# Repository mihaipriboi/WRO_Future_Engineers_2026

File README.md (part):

<center><h1> Nerdvana Cancer 2026 </center>

This repository contains the documentation for the Nerdvana Cancer team's robot for the 2026 World Robot Olympiad Future Engineers competition. The robot, was designed and built by a team of three students.

## Table of Contents
* [The Team](#team)
* [The Challenge](#challenge)
* [The Robot](#robot-image)
* [Performance Video](#video)
* [The Team's Evolution Over the Years](#team-evolution)
  * [2022 Paula (Pretty Awesome Ultra Low Accurate robot) - International (Germany) - 8th Place](#2022-international)
  * [2023 Paula Mia (Pretty Awesome Ultra Low Accurate Minimum Intelligence Augmentation) - National - 1st Place](#2023-national)
  * [2023 Paula Mia 2 (Pretty Awesome Ultra Locomotion Autonomous Mapping Intelligence Augmentation) - International (Panama) - 17th Place](#2023-international)
  * [2024 TBD - National - 1st Place](#2024-national)
  * [2024 MOOYA (Mechanized Optimization for Outstanding Yield and Adaptation) - International (Turkey) - 7th Place](#2024-international)
  * [2025 MOOYA* (Mechanized Optimization for Outstanding Yield and Adaptation) - National - 1st Place](#2025-national)
  * [2025 L.A.C.H.E. (Lightweight Autonomous Carbon-Hybrid Entity) - International](#2025-international)
  * [2026 M.D.S (Memory, Dead-reckoning & Steering) - Current Robot](#2026-current)
* [Mobility Management](#mobility-management)
  * [Powertrain](#powertrain-mechanical)
    * [Drivetrain](#drivetrain-mechanical)
    * [Motor](#motor-mechanical)
    * [Motor Driver](#motor-driver-mechanical)
  * [Steering](#steering-mechanical)
    * [Servo Motor](#servo-motor)
  * [Chassis](#chassis-mechanical)
* [Power and Sense Management](#power-and-sense-management)
  * [Li-Po Battery](#li-po-battery)
  * [Arduino Nano ESP32](#arduino-nano-esp32)
  * [IMU](#imu-sensor)
  * [OpenMV Cam H7 R2](#openmv-cam-rt1062)
  * [Voltage Regulator](#voltage-regulator)
  * [PCB Design](#pcb)
  * [Circuit Diagram](#circuit-diagram)
* [Code for each component](#code-for-each-component)
  * [Drive Motor](#drive-motor-code)
  * [Servo Motor](#servo-motor-code)
  * [Camera](#camera-code)
  * [IMU](#gyro-sensor-code)
* [Obstacle Management](#obstacle-management)
  * [Qualification Round](#quali-management)
  * [Final Round](#final-management)
  * [Additional code](#additional-code)
* [What We Changed This Year](#whats-new)
  * [Tuning and telemetry over WiFi](#wifi-dashboard)
  * [A drift-free gyro that finds its own straight](#self-straight)
  * [Our own localization and route memory](#self-localization)
  * [Rethinking the parking](#smart-parking)
  * [Where this is heading](#next-steps)
* [Robot Construction Guide](#robot-construction-guide)
  * [Step 0: Print the 3D parts](#3d-printing)
  * [Step 1: Assemble the steering system](#steering-system-assembly)
  * [Step 2: Assemble the powertrain](#powertrain-assembly)
  * [Step 3: Attach the electronics](#electronics-attachment)
  * [Step 4: Upload the code](#code-upload)
* [Cost Report](#cost-report)
  * [3D Printing Costs](#3d-printing-costs)
  * [Other Parts Tested](#other-parts-tested)
  * [Tools and Equipment](#tools-and-equipment)
  * [Summary of Costs](#summary-of-costs)
* [Randomizer](#randomizer)
* [Resources](#resources)
  * [3D Models](#3d-models-resources)
  * [Images](#images-resources)
* [License](#copyright)

---

## The Team 

### Priboi Luca Mihai

<b>Age:</b> 20

<b>University:</b> 2nd year, Politehnica University of Bucharest

<b>Description:</b> Hello! I am Mihai! I've been participating at WRO since 2015 and I am very excited to be part of the Nerdvana Romania team. My academic passions are programming, physics and robotics, but I also enjoy playing the piano 🎹, whatching movies 🎬, traveling ✈️ and Formula 1 🏎️🏁.

---

### Bălan Teodor Ovidiu

<b>Age:</b> 20

<b>University:</b> 2nd year, University of Bucharest

<b>Description:</b> Wassup y'all! My name is Teodor, and I love traveling and experiencing new things. Since I was a kid, I've always been drawn to solving puzzles, playing basketball, discovering new inventions, and thinking of creative ways to do things. Also, I know how to do a backflip. 🤠

---

### Orășeanu Andrei

<b>Age:</b> 17

<b>School:</b> 11th grade, Colegiul Național Gheorghe Șincai

<b>Description:</b> Hello! I'm Andrei, and I've been part of WRO since 2023. What pulled me in from the very first season was the part where you build something with your own hands and then have to teach it to think for itself, that moment when the robot finally does the thing on its own never gets old. My main passions are robotics and physics, but outside the workshop I love traveling ✈️, a long game of chess ♟️, and playing basketball 🏀. I joined the team this year wanting to push our self-driving car further than we ever have, and so far it's been exactly the kind of challenge I was hoping for.

---

### Priboi Maria Marcela
<p align="center">
  
  <p align="center">Nerdvana Romania Founder</p>
</p>

<b>Role:</b> Coach

<b>Description:</b> I am a very ambitious person, I like to work hard and to be involved in many projects. I am a very organized person and I like to have everything planned. I am a very sociable person and I like to communicate with people. I am a very responsible person and I like to take care of everything that is happening around me. I am a very creative person and I like to come up with new ideas. I am a very determined person and I like to achieve my goals.

## The Challenge 

The **[WRO 2026 Future Engineers - Self-Driving Cars](https://wro-association.org/)** challenge invites teams to design, build, and program a robotic vehicle capable of driving autonomously on a racetrack that changes dynamically for each round. The competition includes two main tasks: completing laps while navigating randomized obstacles and successfully performing a precise parallel parking maneuver. Teams must integrate advanced robotics concepts such as computer vision, sensor fusion, and kinematics, focusing on innovation and reliability.

This challenge emphasizes all aspects of the engineering process, including:
- **Mobility Management:** Developing efficient vehicle movement mechanisms.
- **Obstacle Handling:** Strategizing to detect and navigate traffic signs (red and green markers) within specified rules.
- **Documentation:** Showcasing engineering progress, design decisions, and open-source collaboration through a public GitHub repository.

Points are awarded based on performance in the challenge rounds, quality of the engineering documentation, and the ability to create an innovative and robust solution. The goal is to inspire STEM learning through real-world robotics applications, teamwork, and creative problem-solving.

Learn more about the challenge [here](https://wro-association.org/wp-content/uploads/WRO-2026-Future-Engineers-Self-Driving-Cars-General-Rules.pdf).

## Photos of our robot M.D.S (the proven L.A.C.H.E. chassis) 

|  |  | 
| :--: | :--: | 
| *Front* | *Back* |
|  |  | 
| *Left* | *Right* |
|  |  | 
| *Top* | *Bottom* |

<br>

## Our video of the robot on [Youtube](https://www.youtube.com/watch?v=aLT0-nPUaAE) 

<br>

# Our Team's Evolution Over the Years 

We have been participating in the Future Engineers category since 2022, the first year it was introduced in Romania. While our team has seen some changes in membership over the years, we have consistently worked together to build on our experiences. Throughout this time, we have grown and evolved, both in our skills and in our approach to robotics, developing increasingly sophisticated strategies and designs with each competition.

|  |  |
| :--: | :--: |
| *2022 National Competition* |
|  |  |
| *2022 International Competition* |
|  |  |
| *2023 National Competition* |
|  |  |
| *2023 International Competition* |
|  |  |
| *2024 National Competition* |
|  |  |
| *2024 International Competition* |
|  |  |
| *2025 National Competition* |
|  |  |
| *2025 International Competition* |
|  |  |
| *2026 Season — same chassis, new software (M.D.S)* |

## 2022 (No Name) - National - 1st Place 
Our first robot, built for the 2022 Future Engineers competition, was a large, bulky, and mostly Lego-based design, building on our previous experience with RobotMission (which was exclusively Lego Mindstorms). We experimented with adding more advanced components, including a Raspberry Pi 3 with a Pi Camera for object detection, a non-Lego motor and servo, and an Arduino to handle the electronics interface. The Raspberry Pi and Arduino communicated through a custom handshake, and we added ultrasonic sensors for wall and object detection.

3D printing was used minimally, mainly to hold components in place, with some parts even “floating” on cables. Cabling was improvised, using standard-length mother-to-mother wires without much organization. Power was supplied by a small battery pack holding six AAA rechargeable cells. Overall, it was a beginner-level robot: heavy, slow, and cumbersome, with limited processing power and a program that was challenging to run efficiently. At this stage, it did not yet have a name, unlike our later tradition of giving each robot an identity.

## 2022 Paula (Pretty Awesome Ultra Low Accurate robot) - International (Germany) - 8th Place 
The idea was mostly the same as our first robot: a Lego-heavy build, but much sturdier than the flimsy predecessor. Electronics were upgraded with a faster Arduino Nano Every, and we added another ultrasonic sensor at the front for wall detection going forward, along with a bigger, stronger servo. The steering system was still imprecise, the motor remained slow, and cables were everywhere (classic “spaghetti style”).

Perhaps the biggest change was the addition of an MPU6050 gyro, which significantly improved driving straight and performing precise maneuvers, a component we would keep in our designs going forward (though we later found even better options).

Despite the imperfections, with a lot of hard work, some fair bit of luck, and sheer motivation, we managed to rank 8th place. Looking back, as we would see in the following year, the other teams were just as inexperienced, but learning quickly, a reminder that Future Engineers is as much about growth as competition.

## 2023 Paula Mia (Pretty Awesome Ultra Low Accurate Minimum Intelligence Augmentation) - National - 1st Place 
This robot was a major tipping point for us. The base and powertrain were still Lego, but nothing like before. They were rigid, smaller, and efficient, using only what was necessary. Mechanically, this is probably my favorite robot, and the most distinct one.

We implemented an AWD system with three differentials (front, back, and a middle differential actuated directly by the motor), which was bigger, more powerful, and faster than before. The camera was upgraded to a PixyCam, removing the need for the Raspberry Pi and allowing the Arduino to handle the input from the trained camera. Crucially, we added two cameras at angles, giving us large coverage of the map.

Electrically, this was a huge leap. We moved from messy cables everywhere to a prototyping board that organized all components, with dedicated, custom-made cables to reach detached components. We also added small but useful features: a display to see data when not connected to a laptop, and a LiPo battery (larger capacity, higher voltage, lighter, smaller, and easily swappable).

Steering angle was still quite bad, and the code was complicated, messy, and hardly consistent, but the AWD system solved a major issue of losing power in turns. We also upgraded the gyro to a BMI088, which we still use today. Overall, smaller than before but still not tiny, this robot showed a significant evolution in mechanical design, electronics, and vision, laying the foundation for our future builds.

## 2023 Paula Mia 2 (Pretty Awesome Ultra Locomotion Autonomous Mapping Intelligence Augmentation) - International (Panama) - 17th Place 
This robot brought major changes to our design. The frame was now fully 3D-printed, replacing the big, flexible Lego structure with a monocoque that was lighter, stiffer, and more compact. However, the wheels, differential, and steering system were still Lego, as printing such small components proved too brittle, introduced friction, and reduced precision (not that Lego is precise anyway).

We experimented with a 360° LiDAR, which in theory allowed us to see all walls and obstacles from any angle at any time. Our main programmer, Teo, wrote brilliant code for detecting them consistently and efficiently. The large LiDAR and its height limitations forced compromises: no AWD system this time, as fitting it alongside the LiDAR was impossible. We also reduced to a single camera, relying on the LiDAR for obstacle detection while the camera captured object color and position for tracking.

Electronics were upgraded to a much faster Teensy microcontroller, offering frequencies magnitudes higher than the Arduino Nano Every. This came with compatibility challenges and sparse documentation, but we managed to make it work. Cable management finally improved, though some wires were still visible. Steering precision improved, but not dramatically.

Going to Panama, we were confident, but color calibration issues due to lighting differences affected performance. The robot was inconsistent, and we managed the situation worse than we could have, resulting in 17th place. Meanwhile, other teams had advanced significantly with brilliant solutions we hadn't considered.

Despite the setback, this experience reinforced the essence of Future Engineers: learning, communicating, and sharing knowledge. We gained as much as we could, returned home, and immediately started designing a new, better robot, determined to surpass everything we had built before.

## 2024 TBD - National - 1st Place 
Oops! We decided to hold off on naming our best robot yet, which resulted in forgetting to give it a proper name at the national competition :). This robot represented the culmination of everything we had learned over the previous two long (at least it felt like it) years in Future Engineers.

Design and mechanics: Lego was minimal, just for mounting the big wheels (which we had been using for a while and saw no reason to change) and the differential (still for friction reasons). Everything else was 3D-printed, modular, and lightweight, made from translucent yellow PLA, our club color. It followed the trend: smaller, lighter, faster, and fully visible, no hidden parts, random Lego pieces, oversized LiDARs, or messy cables.

Electronics and control: We returned to Arduino for better documentation and integration (though that model had firmware issues and could break easily. One could hope!). The microcontroller was an Arduino ESP32 Nano, providing speed and wireless programming capabilities (though we ended up sticking with wired uploading due to web app limitations).

Vision and sensing: We upgraded from the PixyCam to an OpenMV camera, programmable in Python, supporting object detection with machine learning, fine-tuned resolution, FPS, and exposure settings. Distance from cubes and walls was now derived directly from the camera, eliminating the need for distance sensors.

Steering and performance: We built a custom parallelogram steering system, simple but effective. But, with large wheels, a faster motor, and reduced weight, high-speed corners caused the front wheels to skid. To solve this, we added weights over the front of the body, improving friction and stability.

This robot combined all the lessons from past competitions: modularity, lightness, precision, speed, and simplicity. It was the first design where everything we wanted actually came together, setting the stage for our international competition robot later that year.

## 2024 MOOYA (Mechanized Optimization for Outstanding Yield and Adaptation) - International (Turkey) - 7th Place 
This was the same base as our previous national robot (finally with a proper name), with the focus shifting mostly to code refinement. We worked on making the program as efficient and reliable as possible, but mechanical challenges persisted.

Despite being quite light (~300 g), the robot still skidded in high-speed corners. To counteract this, we added weights over the front wheels to improve grip, which caused the rear to lift during acceleration. Adding rear weight again shifted the problem to the front: a vicious cycle. Ultimately, the robot reached almost 600 g, and we also switched to PLA-CF filament (PLA with carbon fibers) for increased strength, which helped the thin steering pieces survive the competition.

Performance at Istanbul ranked us 7th place. It wasn't our highest potential, and while saying we were "disappointed" might be too strong, we were definitely not fully satisfied. Skidding, imprecise steering, and camera issues from auto-exposure and other settings prevented us from performing as well as in testing. This experience highlighted exactly what we needed to focus on for the next edition: minimizing skidding, improving steering precision, and resolving camera reliability issues.

## 2025 MOOYA* (Mechanized Optimization for Outstanding Yield and Adaptation) - National - 1st Place 
For the national competition, we used the same robot with targeted upgrades. The OpenMV camera was replaced with a newer, more powerful model, offering higher resolution, faster FPS, and additional options for object detection. Its microcontroller was upgraded as well, improving processing speed and reliability.

With these changes, we were confident that previous camera issues would be resolved. Other mechanical and design aspects remained the same, allowing us to focus on fine-tuning and testing while simultaneously developing the next-generation robot. This strategy ensured we could maximize performance at the national level while preparing for the next step in our evolution.

## 2025 L.A.C.H.E. (Lightweight Autonomous Carbon-Hybrid Entity) - International 
Following the trend of evolution, our current robot is smaller, faster, more precise, and highly custom-made. Every aspect of the design reflects lessons learned from previous years.

Mechanical design:
- Fully 3D-printed drivetrain and frame using PLA-CF for strength and rigidity.
- Smaller Pololu wheels, chosen for better adherence, lower center of gravity, and compact size.
- Differential and minimal Lego parts retained only where friction made it advantageous.
- Total weight: 220 g, achieving excellent speed without any skidding.

Electronics:
- Designed a custom PCB, replacing previous prototyping boards and making the system more integrated and reliable.
- Custom cables with snap-in headers ensure correct orientation and prevent shorts or miswiring (no more accidental mistakes like in earlier designs).
- The camera is detached and easily repositionable along all axes (horizontal, vertical, and rotation) within seconds, avoiding hours of redesign like before.
- Microcontroller and wiring optimized for minimal weight and maximum performance.

Performance:
- Lightweight and compact, yet mechanically robust.
- Steering and drivetrain tuned for high-speed precision, eliminating skidding problems from previous robots.
- The robot's modularity allows for quick component swaps and adjustments.

This robot represents the culmination of four years of experience: compact, fast, lightweight, and precise. With improved electronics, optimized mechanics, and programmable vision, it's now up to us to make the best of it in the next competitions.

## 2026 M.D.S (Memory, Dead-reckoning & Steering) - Current Robot 
This season we did something we'd never done before: we left the robot alone. L.A.C.H.E. was the first build where the mechanics genuinely weren't the thing holding us back, the drivetrain is smooth, the Ackermann steering is precise, the weight sits where we want it, so re-printing the whole thing just to say we changed something felt like fixing what wasn't broken. Every robot photo in this repository is still that exact chassis, and the construction guide below still builds it part for part.

What changed is the part you can't really photograph. This year's car is L.A.C.H.E.'s body running a completely reworked brain, and that's the reason it earns its own name. **M.D.S** stands for the three ideas that brain is built around: **M**emory, we record the line we drive so we can replay a good lap instead of reacting to every corner from scratch; **D**ead-reckoning, the robot now tracks its own position on the mat from the gyro and the encoder; and **S**teering, the car calibrates its own dead-straight trim from real driving data instead of us dialing it in by hand. It also fits the challenge nicely, a self-driving car that drives from memory and knows where it stands.

All of it is written up in detail in [What We Changed This Year](#whats-new): a drift-free 1000 Hz gyro, a steering center the robot finds on its own, live tuning over WiFi, and the start of our own on-board localization. The short version is that the hardware is the same proven L.A.C.H.E., and the whole of this season went into teaching it to actually know where it is and to drive a line it has already learned.

# Mobility Management 

The robot's mobility is managed by a combination of components, including the powertrain, steering system, and chassis. These elements work together to ensure the robot's smooth and efficient movement.

## Powertrain 

Between the motor and the wheels, there is a 1:2 gear ratio drivetrain that increases the speed of the robot while reducing the torque. This setup allows the robot to reach higher speeds on the track, which is essential for completing laps quickly. It's made by using a 24 teeth gear connected to the motor axle, which drives a 12 teeth gear attached to the differential input axle.

For the differential we used the work of @COPERNICON_359779 on printables.com https://www.printables.com/model/344703-lego-micro-diff-compact-modular-design/files under Creative Commons - Public Domain.

### Drivetrain 

To minimize friction and maximize speed, the drivetrain combines the best of our previous Lego experience with a fully custom, precision-controlled layout. Although most structural elements are now 3D-printed, we still use two Lego axles, but only to connect with the three small internal gears of our custom 3D-printed differential. This keeps the extremely low friction and reliability of Lego's small internal gears while allowing the outer housing, tolerances, and geometry to be fully customized.

Because we transitioned to Pololu wheels, we designed a custom connector that converts the Lego axle interface to a 3 mm D-shaft, ensuring a perfectly centered, secure fit. This allowed us to retain the low-friction Lego internal gear system while benefiting from the superior grip, reduced weight, and lower rotational inertia of Pololu wheels.

The entire drivetrain is tightly enclosed inside the chassis, which was designed around it with minimal clearance. This enclosure reduces backlash, eliminates unnecessary play, and guarantees consistent alignment of the gears and axles. Every internal sliding surface is sanded, bringing friction down to nearly zero and allowing the robot to maintain high speed without compromises in stability or precision.

The result is our most efficient drivetrain yet, compact, lightweight, smooth, and engineered to take full advantage of every bit of power the motor provides.

<br>

**Potential Improvements**:
- Upgrade to a more precise metal differential for smoother turning, which would also remove the need for Lego axles.

### Motor 

<table>
  <tr>
    <td width="50%" style="text-align: left;">
      
    </td>
    <td width="50%" style="text-align: left; vertical-align: top;">
      <h3>Specifications:</h3>
      <li>Voltage: 12V</li>
      <li>Gear Ratio: 30:1</li>
      <li>Speed: 1100 ± 31% rpm</li>
      <li>Torque: 0.39 ± kg·cm</li>
      <li>Weight: 9.5g</li>
      </li>
    </td>
  </tr>
</table>

Following an evaluation of different motors, we settled on a micro DC gear motor on which we attached a magnetic encoder. This motor was selected for its lightweight and compact design, which stands out among others with comparable output. Additionally, the magnetic encoder offers greater precision than its optical counterpart. We secured the motor to the chassis using a Pololu white plastic mounting bracket. As for the wheels, we used Solarbotics RW2i Wheel (internal set screw), which are 28mm diameter wheels with a 3mm D-shaft, rubber tread, and 12.7mm width, which provides excellent traction on the competition surface.

<table>
  <tr>
    <td width="33%" style="text-align: left;">
      
    </td>
    <td width="33%" style="text-align: left; vertical-align: top;">
      
    </td>
    <td width="33%" style="text-align: left; vertical-align: top;">
      
  </tr>
</table>

Where to buy the motor: https://www.pololu.com/product/3039
Where to buy the encoder: https://www.pololu.com/product/4761
Were to buy the motor bracket: https://www.pololu.com/product/1086
Where to buy the wheels: https://www.tme.eu/ro/details/pololu-1127/accesorii-pentru-robotica-si-rc/pololu/?brutto=1&currency=RON&gad_campaignid=10591401989

<br>

**Potential Improvements**:
- Consider upgrading to a brushless motor for higher efficiency and better thermal management.
- Explore batery solutions that can provide higher voltage to the motor for increased speed and torque.

### Motor Driver 

<table>
  <tr>
    <td width="50%" style="text-align: left;">
      
    </td>
    <td width="50%" style="text-align: left; vertical-align: top;">
      <h3>Specifications:</h3>
      <li>Power supply voltage: VM = 15V max, VCC = 2.7--5.5V</li>
      <li>Output current: Iout = 1.2A (average) / 3.2A (peak)</li>
      <li>Standby control to save power</li>
      <li>CW/CCW/short-brake/stop motor control modes</li>
      <li>Built-in thermal shutdown circuit and low-voltage detecting circuit</li>
    </td>
  </tr>
</table>

To control the speed of the drive motor, we utilized a SparkFun Dual TB6612FNG motor driver.

Where to buy the motor driver: https://www.sparkfun.com/products/14450

<br>

**Potential Improvements**:
- Replace the motor driver with a custom PCB to reduce weight and improve space utilization.
- Add active cooling or heat sinks for enhanced thermal performance during extended use.
- Explore higher-current motor drivers to accommodate potential motor upgrades.
- Implement a more robust power management system to ensure reliable operation.

## Steering 

For this robot, we completely redesigned the steering system, moving away from the older parallelogram linkage and finally implementing a true Ackermann steering geometry. This upgrade allows the wheels to follow natural turning arcs, reducing slip during cornering and providing far more predictable handling at high speeds.

A major structural improvement is that the pivot point is now located inside the wheel itself, rather than outside as in previous designs. This drastically increases steering rigidity, improves response time, and eliminates a large portion of the unwanted flex that affected earlier robots.

The joints use 2 mm steel rods, which provide excellent strength-to-weight ratio and near-zero play. However, we changed the geometry of the steering linkages:
the distance between the steering pivot and the tie-rod mounting point is now significantly larger. This was done intentionally to reduce the influence of servo backlash and any free movement in the servo arms. The longer lever arm means that any tiny servo play translates into much smaller unwanted wheel rotation—greatly improving precision, especially when driving straight or making micro-adjustments.

The steering knuckles, tie rod and steering column are all custom 3D-printed and tightly integrated into the chassis. The compact design reduces weight, while the enclosed mounting ensures consistent alignment and minimal lateral movement.

Overall, this is our most precise, responsive, and stable steering system to date: lighter, smoother, and far more accurate than any previous generation.

<br>

**Potential Improvements**:
- Make the steering angle wider to improve the robot's turning radius.
- Use ball-bearing joints in the linkage to reduce friction and increase durability.
- Replace the 3D-printed components with lightweight aluminum for greater strength.

### Servo Motor 

<table>
  <tr>
    <td width="50%" style="text-align: left;">
      
    </td>
    <td width="50%" style="text-align: left; vertical-align: top;">
      <h3>Specifications:</h3>
      <li>Weight: 13.4g</li>
      <li>Stall torque: 2.2 kgf·cm (6V)</li>
      <li>Operating speed: 0.08 s/60 degree (6V)</li>
      <li>Rotation angle: 120 degree</li>
    </td>
  </tr>
</table>

For steering, we selected the MG90S servo motor, favoring it for its high torque and swift response.

Where to buy the servo motor: https://cleste.ro/motor-servo-mg90s-180g.html

<br>

**Potential Improvements**:
- Test servos with a wider rotation angle to improve steering flexibility.
- Integrate position feedback into the servo for real-time adjustment and enhanced precision.

## Chassis 

Over the years, our robots transitioned from bulky, Lego-dominated builds to increasingly custom and lightweight designs. This year, the chassis is now almost entirely 3D-printed, built with PLA-CF (carbon-fiber–reinforced PLA). This material choice drastically improves stiffness, reduces flex under load, and provides far better durability than traditional PLA, especially for thin steering components and structural mounts.

By redesigning every subsystem with minimalism in mind and reducing the number of individual parts, the robot became approximately 50% lighter than last year's version while also being significantly smaller and more compact. This size reduction improves handling, center of gravity, and serviceability.

The entire chassis is tightly integrated so that all drivetrain, steering, and electronic components sit securely with minimal backlash or unwanted movement.

The chassis is organized into clear functional zones:

**Rear Section:** Houses the new custom 3D-printed differential, tightly enclosed to reduce vibrations and friction.

**Central Section:** Contains a dedicated cutout for the Li-Po battery, above which the gyro is screwed in. The custom PCB is mounted above that, screwed into the chassis as well. The compact layout ensures short signal paths and extremely clean cable management.

**Front Section:** Holds the servo motor, steering assembly, and the now movable camera bracket. The camera is mounted on an adjustable multi-axis bracket, allowing quick repositioning in seconds (a task that previously required major redesigns).

Overall, this year's chassis reflects a philosophy of precision, compactness, and complete customization. Every feature, from material choice to structural layout, was designed to minimize weight, reduce friction, and maximize performance.

The Camera Mount is designed to be adjustable along the horizontal axis. It screws into the chassis.

The Camera Bracket is designed to be adjustable along the vertical axis and to rotate. It screws into the Camera Mount. The OpenMV Camera lens is attached to the Camera Bracket using screws.

<br>

**Potential Improvements**:
- Add vibration-damping materials to minimize disturbances during operation.
- Implement a more aerodynamic shape to reduce drag and improve speed (if applicable at its speed).
- Integrate a suspension system to enhance stability when turning.
- Explore the possibility of using cnc aluminium for the chassis for improved durability.
- Add a protective cover to shield the components from dust and debris.

# Power and Sense Management 

The robot's power and sense management system is composed of several components, including a Li-Po battery, an Arduino Nano ESP32, an IMU sensor, and an OpenMV Cam RT1062. These components work together to provide the robot with the necessary power and sensory input to navigate its environment effectively.

### Li-Po Battery 

<table>
  <tr>
    <td width="50%" style="text-align: left;">
      
    </td>
    <td width="50%" style="text-align: left; vertical-align: top;">
      <h3>Specifications:</h3>
      <li>Capacity: 450mAh</li>
      <li>Voltage: 7.4V/2S</li>
      <li>Discharge rate: 30C</li>
      <li>Weight: 33 g</li>
      <li>Size: 56.5*31*9mm</li>
    </td>
  </tr>
</table>

Where to buy the battery: https://hpi-racing.ro/li-po-2s-74v/acumulator-lipo-gens-ace-g-tech-soaring-450mah-74v-30c-2s1p-cu-jst-syp.html

The battery is mounted using a custom 3D-printed holder, which is secured to the chassis.

<br>

**Potential Improvements**:
- Consider using a higher-capacity battery to extend runtime without increasing weight significantly.
- Add a battery management system (BMS) for better charging and discharging safety.
- Implement a battery level indicator to monitor power consumption and remaining charge.

### Arduino Nano ESP32 

<table>
  <tr>
    <td width="50%" style="text-align: left;">
      
    </td>
    <td width="50%" style="text-align: left; vertical-align: top;">
      <h3>Specifications:</h3>
      <li>Microcontroller: ESP32</li>
      <li>Flash memory: 4MB</li>
      <li>SRAM: 520KB</li>
      <li>Frequency: 240MHz</li>
      <li>Pins: 22</li>
      <li>Input voltage: 5V</li>
    </td>
  </tr>
</table>

At previous competitions, we used many microcontrollers to manage the robot's various components. This year, we opted for the Arduino Nano ESP32, which combines the functionalities of an Arduino Nano and an ESP32. This microcontroller is capable of handling all of the robot's sensors and actuators, providing a more streamlined and efficient solution.

Where to buy the Arduino Nano ESP32: https://store.arduino.cc/products/nano-esp32

<br>

**Potential Improvements**:
- Test alternative microcontrollers with additional processing power or I/O pins for future scalability.

### IMU 

<table>
  <tr>
    <td width="50%" style="text-align: left;">
      
    </td>
    <td width="50%" style="text-align: left; vertical-align: top;">
      <h3>Specifications:</h3>
      <li>Gyroscope range: ±2000°/s</li>
      <li>Accelerometer range: ±24g</li>
      <li>Interface: I2C</li>
      <li>Supply voltage: 1.71V to 3.6V</li>
      <li>Current consumption: 0.9mA</li>
    </td>
  </tr>
</table>

One importat aspect that helps the robot navigate is the inertial measurement unit (IMU). This sensor is based on BOSCH BMI088, which is a high-performance IMU with high vibration suppression. While the IMU measure the angular velocity and the acceleration of the robot, we only use the angular velocity to calculate the angle of the robot. The IMU is wired to the SDA and SCL pins and a additional interrupt pin on the arduino.

Where to buy the gyro sensor: https://www.seeedstudio.com/Grove-6-Axis-Accelerometer-Gyroscope-BMI088.html

<br>

**Potential Improvements**:
- Explore alternative IMU sensors with higher accuracy and better vibration resistance.
- Implement sensor fusion with additional sensors (e.g., magnetometer) for enhanced navigation.
- Test calibration procedures to minimize drift over longer runs.

### OpenMV Cam RT1062 

<table>
  <tr>
    <td width="50%" style="text-align: left;">
      
    </td>
    <td width="50%" style="text-align: left; vertical-align: top;">
      <h3>Specifications:</h3>
      <li>Processor: ARM® 32-bit Cortex®-M7 CPU w/ Double Precision FPU</li>
      <li>RAM: 32MB</li>
      <li>Flash memory: 16MB</li>
      <li>Frequency: 600MHz</li>
      <li>Resolution: 2952x1944 (5MP) and under</li>
      <li>Frame rate: 60fps</li>
    </td>
  </tr>
</table>

The OpenMV Cam RT1062 is an improvement from last year's OpenMV Cam H7 R2, in most aspects (rezolution, processing speed, camera settings possibility). The OpenMV is a high-performance camera capable of color tracking. The best feature of this camera compared to other options (like the Pixy cam) is that is has a built-in microcontroller that can process the images and send the results to the Arduino. This way, the Arduino can focus on the robot's movement and the camera can focus on the image processing.

Additionally, we implemented a real-time feedback system using wifi that displays the detected colors and calibrated values on the camera's interface. This allows us to visually verify the accuracy of the color detection and make adjustments if necessary, while the robot is running.

Together with the Arduino Nano ESP32, the camera delivers readings at approximately 60 frames per second.

In order to have the lens separated from the camera body, we used the Camera Module Extension Cable

Where to buy the OpenMV Cam RT1062: https://openmv.io/products/openmv-cam-rt
Where to buy the Camera Module Extension Cable: https://openmv.io/products/camera-module-extension-cable

<br>

**Potential Improvements**:
- Test alternative lighting solutions to improve visibility in various conditions.
- Implement advanced image processing algorithms to enhance detection accuracy.
- Use color correction algorithms: Apply color correction algorithms to compensate for any variations in lighting conditions. These algorithms can adjust the color values of the captured image to match a reference color space, making the colors more consistent and easier to calibrate.

### Voltage regulator 

<table>
  <tr>
    <td width="50%" style="text-align: left;">
      
    </td>
    <td width="50%" style="text-align: left; vertical-align: top;">
      <h3>Specifications:</h3>
      <li>Input voltage: 35V max</li>
      <li>Output voltage: 5V</li>
      <li>Output current: 1.5A</li>
      <li>Thermal shutdown circuit</li>
      <li>Short-circuit protection</li>
    </td>
  </tr>
</table>

To provide the Arduino Nano ESP32 with the required 5V, we needed to decrease the output from the 7.4V battery, which can reach up to 8.4V when fully charged. We employed a linear voltage regulator, the L7805CV, capable of converting input voltages below 35V down to a steady 5V.

Where to buy the 5V voltage regulator: https://ro.mouser.com/ProductDetail/STMicroelectronics/L7805CV?qs=9NrABl3fj%2FqplZAHiYUxWg%3D%3D

<br>

**Potential Improvements**:
- Replace the linear voltage regulator with a switching regulator for better efficiency.
- Add heat sinks to the regulator for improved thermal management.

### PCB design 

The robot's PCB was designed using KiCad software. The PCB integrates the voltage regulator, headers for connecting the Arduino Nano ESP32, motor driver, and camera body directly on it. We used headers in order to make the connections modular and easy to disassemble if needed for maintenance or upgrades. The PCB also includes connectors for the battery, motor, servo, and IMU sensor.

| PCB Rendered |
| :--: |
|  | 
| Empty PCB |
|  | 
| PCB |
|  |

Where we bought the PCB: https://jlcpcb.com/

<br>

**Potential Improvements**:
- Integrate debugging points on the PCB to simplify troubleshooting.

### Circuit diagram 

<br>

# Code for each component 

## Drive Motor 

The motor driver can be directly managed with a single PWM pin that adjusts the motor's speed and two digital pins designated for determining the motor's rotation direction. Consequently, the use of any external library for motor manipulation was unnecessary.

We devised two functions within our control system: one to modify the motor's velocity and another to halt it effectively, incorporating a braking feature. To achieve this, we convert the desired speed from our established scale of -100 to +100 to the PWM equivalent of 0 to 1023. The motor's direction is then adjusted according to the sign of the input value.

Given the fact that the Arduino has an ESP chip, the PWM signals have to be sent using the ```ledc``` utility.

```ino
void motor_driver_setup() {
  ledcSetup(DRIVER_PWM_CHANNEL, PWM_FREQ, PWM_RES);
  ledcAttachPin(PWMA, DRIVER_PWM_CHANNEL);

  pinMode(AIN1, OUTPUT);
  pinMode(AIN2, OUTPUT);
}

void move_motor(double speed) {  // move the motor with a given speed in the [-100, 100] interval
  int dir = 1;
  if (speed < 0) {
    dir = -1;
    speed *= -1;
  }
  else if (speed == 0) {
    dir = 0;
  }
  speed = map_double(speed, 0, 100, 0, 1023);
  if (dir == 1) { // move the motor forward
    digitalWrite(AIN1, HIGH);
    digitalWrite(AIN2, LOW);
  }
  else if (dir == -1) { // move it backwards
    digitalWrite(AIN1, LOW);
    digitalWrite(AIN2, HIGH);
  }
  else { // implement active break (not used since we don't know how reliable it is)
    digitalWrite(AIN1, LOW);
    digitalWrite(AIN2, LOW);
  }
  ledcWrite(DRIVER_PWM_CHANNEL, (int)speed); // write the speed using PWM
}

void motor_break(long long break_time) { // stop the robot for a given time
  move_motor(-3);
  custom_delay(break_time);
}
```

However, for the encoder, we required a specialized library to handle the more complex signal processing. The library we use for interfacing with the encoder is called ```Encoder.h```.

The encoder operates with a straightforward function that we found easy to comprehend and program. In order to determine the distance in cm, we divided the returned value by 12, since the encoder measures 12 counts per revolution. Then we multiplied this with the gear ratio, wheel diameter and Pi. After that we divided by 10 to convert to cm.

Because of the way the ESP32 chip interacts with the components, in order for this library to properly work, we should select the pin numbering option as "by GPIO number", not as the default "by Arduino pin".

```ino
double read_motor_cm() {  // getting the distance driven by the motor in cm
  return GEAR_RATIO * WHEEL_DIAM * M_PI * (double)myEnc.read() / 12 / 10;
}
```

## Servo Motor 

For controlling the servo motor, we utilize the ```Servo.h``` library, which provides the necessary functions to manage the servo's movements. Initially, we configure the servo by establishing its range, defining the maximum and minimum angles it can achieve in both directions. This ensures that we can accurately position the servo within its operational limits.

```ino
void servo_setup() {
  // attach the servo to the right pin and move it to the minimum and maximum angles
  // in the end, center the servo so that we start the program moving straight
  servo.attach(SERVO_PIN);
  for (int deg = servo.read() - 1; deg >= ANGLE_MIN; deg--)
    servo.write(deg);
  custom_delay(500);
  // Serial.println("after ANGLE_MIN");
  for (int deg = servo.read() + 1; deg <= ANGLE_MID; deg++)
    servo.write(deg);
  // Serial.println("after ANGLE_MID");
  for (int deg = servo.read() + 1; deg <= ANGLE_MAX; deg++)
    servo.write(deg);
  custom_delay(500);
  // Serial.println("after ANGLE_MAX");
  for (int deg = servo.read() - 1; deg >= ANGLE_MID; deg--)
    servo.write(deg);
  custom_delay(500);
  // Serial.println("after ANGLE_MID");
  goal_deg = ANGLE_MID;
}
```

The servo motor is controlled dinamically in the loop by setting a goal angle and taking small steps towards that goal at every iteration. This way we make sure that we can send a lot of fast angle changes to the servo and get the wanted results.

The function ```move_servo``` sets the goal angle to the given parameter. If the angle is negative the motor will rotate to the right, and if it is positive, the motor will rotate to left. This way, 0 is going to be the position in which the wheels are straight. Also, the values given the motor need to be between -1 and 1, so we use a clamp function to limit the value we are going to give the motor to rotate to and an interval mapping function to map the parameter from the [-1; 1] interval to the [ANGLE_MIN; ANGLE_MAX] interval.

The function ```update_servo``` takes a small step towards the goal angle as described above.

```ino
void move_servo(double angle) {  // move the servo to the angle checkpoint by setting the goal degrees to the angle value
  goal_deg = map_double(angle, -1, 1, ANGLE_MIN, ANGLE_MAX);
}

void update_servo() { // update the servo, making it closer to the goal angle by a small step
  int current_angle_servo = servo.read();
  if (abs(current_angle_servo - goal_deg) >= ANGLE_VARIANCE_THRESHOLD) { // if we're too far off, directly write the new angle
    servo.write(goal_deg);
  }
  else {
    // increment the angle with a small step in the right direction
    // making sure we don't exceed our angle limitations
    if (current_angle_servo < goal_deg) {
      servo.write(min(current_angle_servo + STEP, ANGLE_MAX));
    }
    else if (current_angle_servo > goal_deg) {
      servo.write(max(current_angle_servo - STEP, ANGLE_MIN));
    }
  }
}

void loop() {
  // other code
  update_servo();
}
```

## Camera 

Now that we finished implementing the functions that we need to make the robot move and steer, we have to make it see the lines that trigger the turns, the cubes and the parking walls and move accordingly. To communicate with the camera, we use the ```UART``` protocol. In order for this to work, we must link the ```RX0``` pin on the arduino (the receiver pin) to the ```P4``` pin on the camera (the transmitter pin) and the ```TX1``` pin on the arduino (the transmitter pin) to the ```P5``` pin on the camera (the receiver pin). In addition, the baud rates from the ```Serial0``` object on the arduino and the ```uart``` object on the camera must match.

**Arduino code:**

```ino
void comm_setup() {
  Serial.begin(9600);
  // while(!Serial);
  blink_led(LED_BUILTIN, 500);

  Serial0.begin(19200);
  while(!Serial0); // wait for the serial to properly initialize
  blink_led(LED_BUILTIN, 500);
  receivedMessage = "";
}

void loop() {
  // execute pending commands
  while (Serial0.available() > 0) { // if we have some characters waiting
    char receivedChar = Serial0.read(); // we get the first character
    if (receivedChar == '\n') { // if it's the end of message marker
      if (CASE != PARK) { // if we want to execute commands
        execute(receivedMessage); // execute the received command from the OpenMV camera
      }
      receivedMessage = ""; // reset the received message
    }
    else {
      receivedMessage += receivedChar; // append characters to the received message
    }
  }
}
```

**Camera code:**

```py
# setup UART connection to arduino
uart = UART(3, 19200)
# 3 - the uart config, meaning that we use pins P4 as the transmitter, P5 as the receiver
# 19200 - baud rate aka frequency, must match the one set up on the arduino

# because we have a one-sided communication going on
# we can directly write messages without any supplementary checks
uart.write(msg)
```

In order to detect colors, we have to take pictures in which to search for colors. This is the sequence that sets up the camera sensor. Due to the limitations of the sensor, we couldn't manually adjust the white balance, gain, exposure time or access its registries.

```py
import sensor

# initialize the sensor
sensor.reset()
sensor.set_pixformat(sensor.RGB565)
sensor.set_framesize(sensor.QQVGA)
#sensor.set_framerate(40)
sensor.set_vflip(True)
sensor.set_hmirror(True)

# disable auto gain, white balance, and exposure
sensor.set_auto_gain(False)  # must be turned off for color tracking
sensor.set_auto_whitebal(False)  # must be turned off for color tracking
sensor.set_auto_exposure(False, exposure_us=10000) # set constant exposure for the best visibility

# skip some frames to let the camera adjust
sensor.skip_frames(time=2000)
```

Now for the camera logic, the color tracking is pretty simple: the camera can return blobs of pixels that fit into a certain ```LAB``` threshold representing a color. We can also restrain the blob detection to a rectangle of interest and apply pixel count, bounding rectangle area and density filters as well. The reason for which we do this, is that certain colors, like green, red, blue and orange are pretty common, therefore we don't want the camera to interpret clothes or other objects outside of the map as obstacles. In addition, the orange and red colors, in some light conditions, are quite similar. This is why we apply the pixel count, bounding rectangle area and density filters, to ensure that we are seeing the correct object.

For quali we firstly scan the color of the first seen line. This will give us the direction of the run. Then, we constantly look out for lines that are over a certain area. Once we find one, we send the turn trigger to the Arduino via ```UART```.

```py
while (True):
    clock.tick()
    img = sensor.snapshot()

    # find the coloured blobs corresponding to the turn lines
    orange_blobs = img.find_blobs(orange_threshold, roi=lines_roi, pixels_threshold=line_blob_size, area_threshold=line_blob_size, merge=True)
    blue_blobs = img.find_blobs(blue_threshold, roi=lines_roi, pixels_threshold=line_blob_size, area_threshold=line_blob_size, merge=True)

    orange_blob_w = None
    orange_blob_h = None
    max_width = 0
    max_height = 0
    for blob in orange_blobs:
        if blob.w() >= img.width() * 0.4: # if it meets the minimum width requirement
            if blob.w() > max_width: # if it's the biggest blob yet
                max_width = blob.w()
                orange_blob_w = blob # biggest blob on the width
        if blob.h() >= lines_roi[3] * 0.4: # if it meets the minimum height requirement
            if blob.h() > max_height: # if it's the biggest blob yet
                max_height = blob.h()
                orange_blob_h = blob # biggest blob on the height
    # if we have a blob meeting either the minimum width or height requirement we remember it
    orange_blob = orange_blob_w
    if not orange_blob:
        orange_blob = orange_blob_h

    blue_blob_w = None
    blue_blob_h = None
    max_width = 0
    max_height = 0
    for blob in blue_blobs:
        if blob.w() >= img.width() * 0.4: # if it meets the minimum width requirement
            if blob.w() > max_width: # if it's the biggest blob yet
                max_width = blob.w()
                blue_blob_w = blob # biggest blob on the width
        if blob.h() >= lines_roi[3] * 0.4: # if it meets the minimum height requirement
            if blob.h() > max_height: # if it's the biggest blob yet
                max_height = blob.h()
                blue_blob_h = blob # biggest blob on the height
    # if we have a blob meeting either the minimum width or height requirement we remember it
    blue_blob = blue_blob_w
    if not blue_blob:
        blue_blob = blue_blob_h

    if direction == 0: # if we didn't set a turn direction yet
        if orange_blob: # if the first line we saw was an orange one
            direction = 2
        elif blue_blob: # if the first line we saw was a blue one
            direction = 1

    has_line = False
    if orange_blob or blue_blob: # if we saw either coloured lines, we can make a turn
        has_line = True

    if has_line:
        # if we must turn, send the turn trigger
        uart.write(str(direction) + '\n')
```

## IMU 

To utilize the gyro sensor, we needed to include the ```BMI088.h``` library. During initialization, we allocate a 10-second window to measure the sensor's drift, allowing us to refine the robot's angular readings for greater precision. Additionally, we configure the sensor's output data rate to 400Hz and set the bandwidth to 47Hz. The bandwidth determines the frequency of data sampling by the sensor; a higher bandwidth yields more precise data at the cost of increased power consumption. We also designate pin A6 as an input and attach an interrupt to it, enabling us to capture data from the sensor as soon as it becomes available.

```ino
void gyro_setup(bool debug) {
  int status = accel.begin();
  status = accel.setOdr(Bmi088Accel::ODR_200HZ_BW_80HZ);
  status = accel.pinModeInt1(Bmi088Accel::PUSH_PULL,Bmi088Accel::ACTIVE_HIGH);
  status = accel.mapDrdyInt1(true);

  status = gyro.begin();

  status = gyro.setOdr(Bmi088Gyro::ODR_400HZ_BW_47HZ);
  status = gyro.pinModeInt3(Bmi088Gyro::PUSH_PULL,Bmi088Gyro::ACTIVE_HIGH);
  status = gyro.mapDrdyInt3(true);

  pinMode(INT_PIN,INPUT);
  attachInterrupt(INT_PIN,gyro_drdy,RISING);

  if(status < 0) {
    if(debug){
      Serial.print("BMI Initialization Error!  error: ");
      Serial.println(status);
    }
  }
  else  {
    // Gyro drift calculation
    if(debug) Serial.println("Starting gyro drift calculation...");

    gx = 0;
    // gy = 0;
    // gz = 0;

    gyro_last_read_time = millis();

    double start_time = millis();
    while(millis() - start_time < DRIFT_TEST_TIME * 1000) {
      gyro.readSensor();
      double read_time = millis();
      gx += (gyro.getGyroX_rads() * (read_time - gyro_last_read_time) * 0.001);
      // gy += (gyro.getGyroY_rads() * (read_time - gyro_last_read_time) * 0.001);
      // gz += (gyro.getGyroZ_rads() * (read_time - gyro_last_read_time) * 0.001);

      gyro_last_read_time = read_time;
    }

    drifts_x = gx / DRIFT_TEST_TIME;
    // drifts_y = gy / DRIFT_TEST_TIME;
    // drifts_z = gz / DRIFT_TEST_TIME;

    if(debug) Serial.print("Drift test done!\nx: ");
    if(debug) Serial.println(drifts_x, 6);
    // if(debug) Serial.print("   y: ");
    // if(debug) Serial.print(drifts_y, 6);
    // if(debug) Serial.print("   z: ");
    // if(debug) Serial.println(drifts_z, 6);
  }
  // Gyro value reset
  gx = 0;
  // gy = 0;
  // gz = 0;

  gyro_last_read_time = millis();
}
```

Within the ```read_gyro``` function, we're retrieving data from the gyro sensor and adjusting it to account for any detected drift, enhancing the accuracy of the readings. Since the gyro provides data in radians, a conversion to degrees is necessary for our application. We're focusing solely on the rotation around the x-axis, hence we only compute the ```gx``` value, which represents the robot's angular rotation in degrees on that specific axis.

```ino
void read_gyro(bool debug) {
  if(gyro_flag) {
    gyro_flag = false;
    gyro.readSensor();   
    double read_time = millis();

    gx += ((gyro.getGyroX_rads() - drifts_x) * (read_time - gyro_last_read_time) * 0.001) * 180.0 / PI;
    // gy += ((gyro.getGyroY_rads() - drifts_y) * (read_time - gyro_last_read_time) * 0.001) * 180.0 / PI;
    // gz += ((gyro.getGyroZ_rads() - drifts_z) * (read_time - gyro_last_read_time) * 0.001) * 180.0 / PI;

    gyro_last_read_time = read_time;

    if(debug) {
      Serial.print("Gyro: gx: ");
      Serial.println(gx);
      // Serial.print(" gy: ");
      // Serial.print(gy);
      // Serial.print(" gz: ");
      // Serial.println(gz);
    }
  }
}
```

<br>

# Obstacle Management 

## Qualification Round 

For the qualifying round, we set up a basic switch-case system to guide our robot. This system tells the robot what to do next, depending on where it is. The robot knows where it is by counting how many times it has turned.

We use two main switch cases: ```PID``` and ```STOP_QUALI```.

In the ```PID``` case, the robot moves straight and turns. It uses a special tool (PID controller) with a gyro sensor to stay on a straight line. If it sees a corner line, it gets a trigger from the camera to make a turn by adding 90 degrees to the goal angle.

```ino
case PID: {
  check_and_execute_turnaround(gx);
  double err = current_angle_gyro - gx;
  if (millis() - last_rotate > FIRST_STOP_DELAY && turns >= 12) { // if we did 3 runs of the round
    if (FINAL) {
      CASE = STOP_BEFORE_FIND_PARKING; // we need to stop and search for the parking
    }
    else {
      CASE = STOP_QUALI; // stop, challenge over
    }
  }
  else {
    // classic pid on the gyro so that we can move straight
    pid_error_gyro = (err) * kp_gyro + (pid_error_gyro - pid_last_error_gyro) * kd_gyro;
    pid_last_error_gyro = pid_error_gyro;
    move_servo(pid_error_gyro);
  }
  move_motor(MOTOR_SPEED);
  break;
}

case STOP_QUALI: {
  // we finished the challenge, stop the robot
  move_until_angle(MOTOR_SPEED, current_angle_gyro);
  move_cm_gyro(10, MOTOR_SPEED, current_angle_gyro);
  is_running = false;
  Serial.println("Stop case");
  motor_break(1000000000);
}
```

### Line Detection

## Final Round 

For the final round, we based our controller algorithm on the quali code, adding a PID controller on the camera to follow the closest cube until it is in its proximity. In order to get the closest cube to the robot we just search for the biggest red or green coloured blob in the image.
After we're in the cube's proximity, we send a trigger from the camera to the arduino with the cube color so that we can start avoiding it.

```py
img = sensor.snapshot()

# find the coloured blobs corresponding to the cubes
red_blobs = img.find_blobs(red_threshold, roi=cubes_roi, pixels_threshold=min_cube_size, area_threshold=min_cube_size, merge=True)
green_blobs = img.find_blobs(green_threshold, roi=cubes_roi, pixels_threshold=min_cube_size, area_threshold=min_cube_size, merge=True)

msg = "0\n"
max_area = 0
color = 'none'
saved_cube = None
for blob in red_blobs: # for every red blob
    # if they're passing the height and density filters
    # we're keeping the biggest one and its color
    if is_cube(blob, orange_blob, parking_blobs) and blob.area() > max_area:
        max_area = blob.area()
        saved_cube = blob
        color = 'red'
for blob in green_blobs: # for every green blob
    # if they're passing the height and density filters
    # we're keeping the biggest one and its color
    if is_cube(blob, blue_blob, parking_blobs) and blob.area() > max_area:
        max_area = blob.area()
        saved_cube = blob
        color = 'green'

if saved_cube != None: # if we saw a cube
    # if the cube area is over a certain threshold
    # it means we must avoid the cube as we are too close to it
    if (color == 'red' and saved_cube.pixels() >= max_cube_size_red) or (color == 'green' and saved_cube.pixels() >= max_cube_size_green):
        # send the right trigger
        if color == 'red':
            uart.write('R\n')
        else:
            uart.write('G\n')
        if has_line:
            # if we must also turn, send the trigger
            uart.write(str(direction) + '\n') # send the turn trigger
    else: # if the cube isn't too big we must follow it
        # calculate the angle using PID
        err = saved_cube.cx() - img.width() / 2
        steering = err * kp + (err - err_old) * kd
        steering = -clamp(steering, -1, 1)
        err_old = err
        # craft the command
        if color == 'red':
            msg = 'r' + str(steering) + '\n'
        else:
            msg = 'g' + str(steering) + '\n'
        uart.write(msg) # send the message
        if has_line:
            # if we must also turn, send the turn trigger
            uart.write(str(direction) + '\n')
elif has_line: # if we don't see any cubes
    # if we must turn, send the turn trigger
    uart.write(str(direction) + '\n')
```

### Cube Detection

---

The arduino part is quite simple, consisting of the quali switch but with two extra cases: ```FOLLOW_CUBE``` and ```AFTER_CUBE```. In the ```FOLLOW_CUBE``` case we just write to the servo the steering angle calculated by the PID algorithm ran on the camera. After we get the proximity trigger from the camera, we have a custom function called ```pass_cube``` which steers us away from the cube and puts us in the ```AFTER_CUBE``` state. This case consists of two substates: in the first one the robot steers in the opposite direction to center itself again and the second one in which the robot uses a PID with the gyro to move an additional distance so that we're perfectly positioned to see the next cube. After that, we go back to the default ```PID``` case that is used in the quali code.

```ino
// hardcoded sequence that avoids a cube
void pass_cube(int cube_last) {
  int angle_addition = 0;
  if (cube_last == 1) // due to a slight asymmetry in the steering, when avoiding red cubes we need to steer less
    angle_addition = -9;
  read_gyro(false);
  int start_angle = gx;
  move_until_angle(MOTOR_SPEED, start_angle - cube_last * (AVOIDANCE_ANGLE + angle_addition)); // steer away from the cube
  // gain some distance
  if (abs(current_angle_gyro - start_angle) >= 10) // if we passed by it while crooked in regards to the goal line we need to overcompensate in order to see the next cube
    move_cm_gyro(16, MOTOR_SPEED, start_angle - cube_last * (AVOIDANCE_ANGLE + angle_addition));
  else
    move_cm_gyro(7, MOTOR_SPEED, start_angle - cube_last * (AVOIDANCE_ANGLE + angle_addition));
  CASE = AFTER_CUBE;
}
```

```ino
case FOLLOW_CUBE: {
  check_and_execute_turnaround(gx);
  if (millis() - last_rotate > FIRST_STOP_DELAY && turns >= 12) { // if we did 3 runs of the obstacle round, we need to stop and search for the parking
    CASE = STOP_BEFORE_FIND_PARKING;
  }
  else {
    if (millis() - last_follow_cube > FOLLOW_CUBE_DEAD_TIME) // if we lost the cube, we just go back to the default PID case
      CASE = PID;
    // write to the servo the pid computed on the camera in order to follow the cube
    move_servo(follow_cube_angle);
    move_motor(MOTOR_SPEED);
  }
  break;
}

case AFTER_CUBE: {
  check_and_execute_turnaround(gx);
  if (millis() - last_rotate > FIRST_STOP_DELAY && turns >= 12) { // if we did 3 runs of the obstacle round, we need to stop and search for the parking
    CASE = STOP_BEFORE_FIND_PARKING;
  }
  else {
    double err = current_angle_gyro - gx + cube_last * CORRECTION_ANGLE;
    if (abs(err) < 5) {
      // after we avoid the cube, move forward a bit more so that we're positioned
      // to see the next cube
      if (cube_last == turn_direction) // compensate less on the inside
        move_cm_gyro(5, MOTOR_SPEED, current_angle_gyro + cube_last * CORRECTION_ANGLE);
      else
        move_cm_gyro(10, MOTOR_SPEED, current_angle_gyro + cube_last * CORRECTION_ANGLE);
      CASE = PID;
    }
    else {
      // classic pid on the gyro so that we can move in the opposite direction
      // so that we can see the next cube
      pid_error_gyro = (err) * kp_gyro + (pid_error_gyro - pid_last_error_gyro) * kd_gyro;
      pid_last_error_gyro = pid_error_gyro;
      move_servo(pid_error_gyro);
    }
  }
  move_motor(MOTOR_SPEED);
  break;
}
```

The next challenge in this round consists in the final turnaround. If the last seen cube is red, we need to do a roundabout and complete the last lap in the opposite direction. The way we deal with this is a function that checks if we should turn around and executes it if necessary. This function is called in the ```PID```, ```FOLLOW_CUBE``` and ```AFTER_CUBE``` cases.

```ino
void check_and_execute_turnaround(double gx) {
  // if we didn't do the turnaround yet
  // and we did 2 runs of the map
  // and the last seen cube is red
  // and some time passed since the 8th turn
  // (so that we can see the first cube in the starting sequence in case this sequence had 2 cubes and we spawned between them)
  if (!FINAL)
    return;
  if (!TURNED && turns == 8 && cube_last == 1 && millis() - last_rotate > TURNAROUND_DELAY) { // may have to take out the time condition for any case except AFTER_CUBE
    move_until_angle(MOTOR_SPEED, current_angle_gyro + turn_direction * TURNAROUND_ANGLE);
    if (-cube_last == turn_direction) { // if i avoided the cube on the inside, i don't have too much room
      move_cm_gyro(5, MOTOR_SPEED, current_angle_gyro + turn_direction * TURNAROUND_ANGLE); // position ourselves so that we have room to turn around
    }
    else {
      move_cm_gyro(17, MOTOR_SPEED, current_angle_gyro + turn_direction * TURNAROUND_ANGLE); // position ourselves so that we have room to turn around
    }
    turn_direction *= -1;
    current_angle_gyro += turn_direction * 180;
    move_until_angle(MOTOR_SPEED, current_angle_gyro + turn_direction * TURNAROUND_ANGLE);
    TURNED = true;
    CASE = PID;
  }
}
```

The final challenge in this round consists in parking the robot. The way we implement this is based on the quali. Basically we want to move as close to the outer walls as possible so that we're perfectly positioned for the parking and avoid all of the cubes. How we achieve this is by going perpendicular to the outside walls after we finish the obstacle round (see the ```POSITION_BEFORE_FIND_PARKING``` case). The goal is to position ourselves as close as possible to them. After we receive a trigger from the camera saying that we're in its proximity, we straighten ourselves out and start the basic quali code.

While moving around the map like this (in the ```FIND_PARKING``` case), we are constantly scanning for magenta blobs that represent the parking walls. When we detect them, we send a trigger from the camera to the arduino and then we have a hardcoded sequence that puts us between the walls, perfectly parallel to them, implemented in the ```POSITION_FOR_PARK``` case. After that, we move straight in order to get closer to the outer wall (see the ```PARK``` case). When we receive the trigger from the camera, move a couple of cm straight and stop the robot.

Camera code:

```py
# find the coloured blobs corresponding to the parking walls
parking_blobs = img.find_blobs(parking_threshold, roi=parking_roi, pixels_threshold=parking_blob_size_min, area_threshold=parking_blob_size_min, merge=True)
parking_wall_blob = get_biggest_blob(parking_blobs)

# find the coloured blobs corresponding to the outside walls
wall_blobs = img.find_blobs(black_threshold, roi=wall_roi, pixels_threshold=wall_blob_size, area_threshold=wall_blob_size, merge=True)
outer_wall = get_biggest_blob(wall_blobs)

if is_parking_wall(parking_wall_blob):
    # if we saw the parking walls, send the parking trigger
    uart.write('P\n')
if wall_blobs:
    # if the wall is big enough, send a slightly different message that helps us when parking
    # if not, send the classic one
    if outer_wall.pixels() >= wall_roi_area and outer_wall.area() >= wall_roi_area:
        uart.write('WP\n')
    else:
        uart.write('W\n')
```

### Parking Wall Detection

---

**Arduino code:**

```ino
case STOP_BEFORE_FIND_PARKING: {
  // straighten ourselves, start searching for the parking
  motor_break(1000);
  CASE = POSITION_BEFORE_FIND_PARKING;
  break;
}

case POSITION_BEFORE_FIND_PARKING: {
  // classic pid on the gyro so that we can move perpendicular to the walls
  // we don't just call the move_until_angle function so that we can still execute commands
  double err = current_angle_gyro - gx - turn_direction * 90;
  pid_error_gyro = (err) * kp_gyro + (pid_error_gyro - pid_last_error_gyro) * kd_gyro;
  pid_last_error_gyro = pid_error_gyro;
  move_servo(pid_error_gyro);
  move_motor(MOTOR_SPEED);
  break;
}

case FIND_PARKING: {
  // classic pid on the gyro so that we can move straight
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
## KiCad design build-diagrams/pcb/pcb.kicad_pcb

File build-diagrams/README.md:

# Build Diagrams

Includes wiring diagrams, schematics, PCB layouts, and block diagrams related to electrical or logical design.

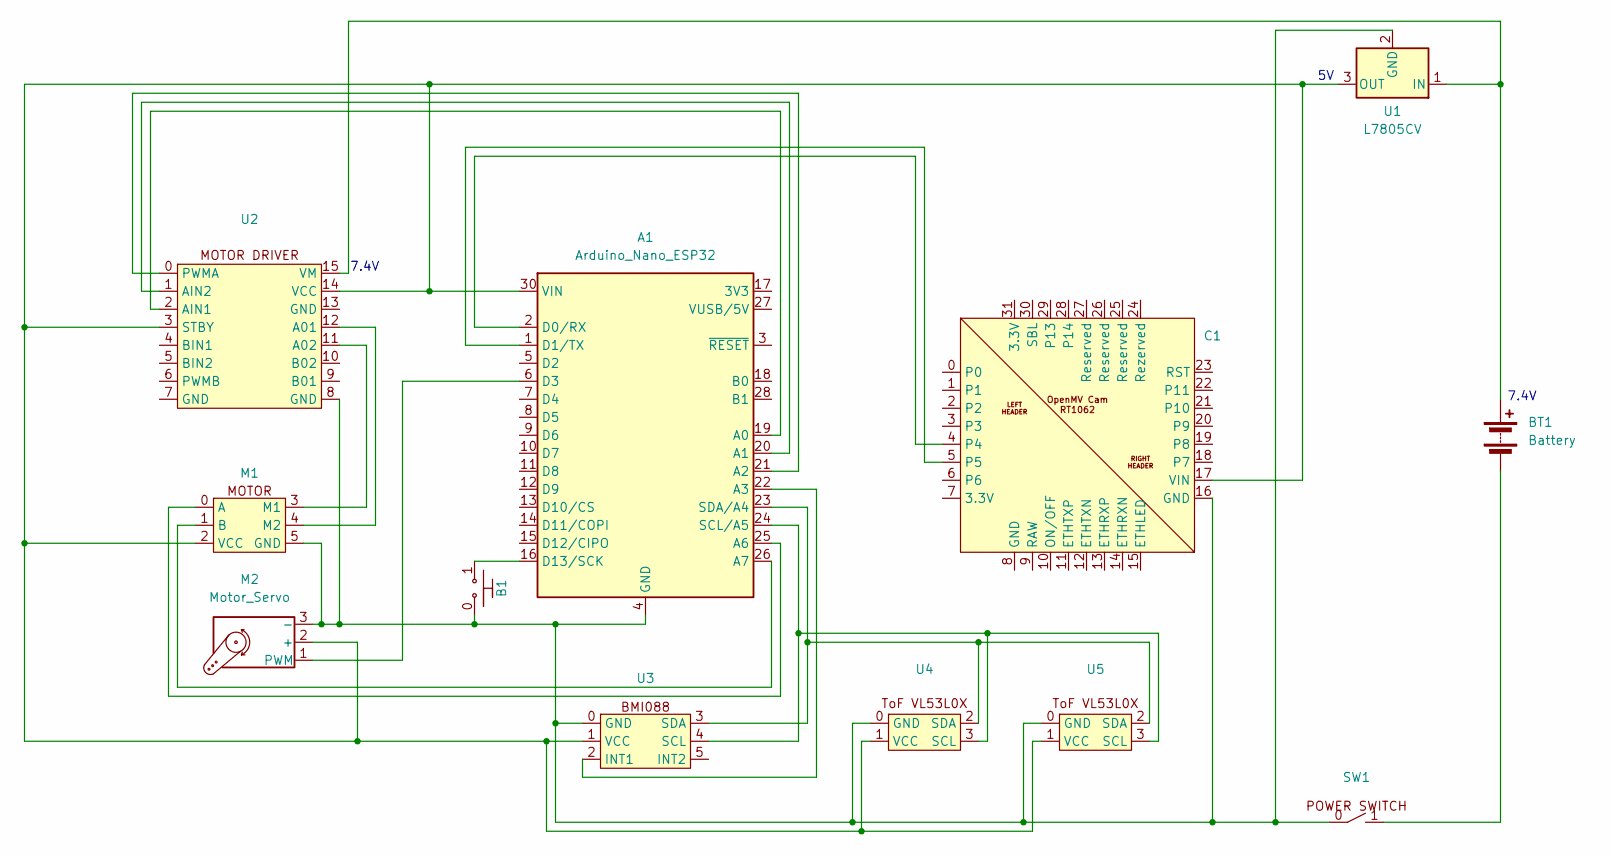
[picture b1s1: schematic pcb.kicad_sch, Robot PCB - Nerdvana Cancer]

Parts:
A1: Arduino_Nano_ESP32; Arduino_Nano
B1: Start Button
BT1: Battery
C1: OPENMV_H7
M1: DC_GEARMOTOR
M2: Motor_Servo; Servo Motor
SW1: Switch
U1: L7805CV
U2: Motor Driver
U3: BMI088
U4, U5: ToF_VL53L0X

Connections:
unnamed: A1.19 (A0), U2.2 (AIN1)
unnamed: A1.20 (A1), U2.1 (AIN2)
unnamed: A1.21 (A2), U2.0 (PWMA)
unnamed: A1.22 (A3), U3.2 (INT1)
unnamed: A1.25 (A6), M1.0 (A)
unnamed: A1.26 (A7), M1.1 (B)
unnamed: A1.2 (D0/RX), C1.4
unnamed: A1.1 (D1/TX), C1.5
unnamed: A1.6 (D3), M2.1 (PWM)
unnamed: A1.16 (D13/SCK), B1.1
unnamed: A1.24 (SCL/A5), U3.4 (SCL), U4.3 (SCL), U5.3 (SCL)
unnamed: A1.23 (SDA/A4), U3.3 (SDA), U4.2 (SDA), U5.2 (SDA)
unnamed: A1.30 (VIN), C1.17 (VIN), M1.2 (VCC), M2.2 (+), U1.3 (OUT), U2.3 (STBY), U2.14 (VCC), U3.1 (VCC), U4.1 (VCC), U5.1 (VCC)
unnamed: BT1.1 (+), U1.1 (IN), U2.15 (VM)
unnamed: BT1.2 (-), SW1.1
unnamed: A1.4 (GND), A1.29 (GND), B1.0, C1.16 (GND), M1.5 (GND), M2.3 (-), SW1.0, U1.2 (GND), U2.8 (GND), U3.0 (GND), U4.0 (GND), U5.0 (GND)
unnamed: M1.3 (M1), U2.11 (A02)
unnamed: M1.4 (M2), U2.12 (A01)

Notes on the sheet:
7.4V

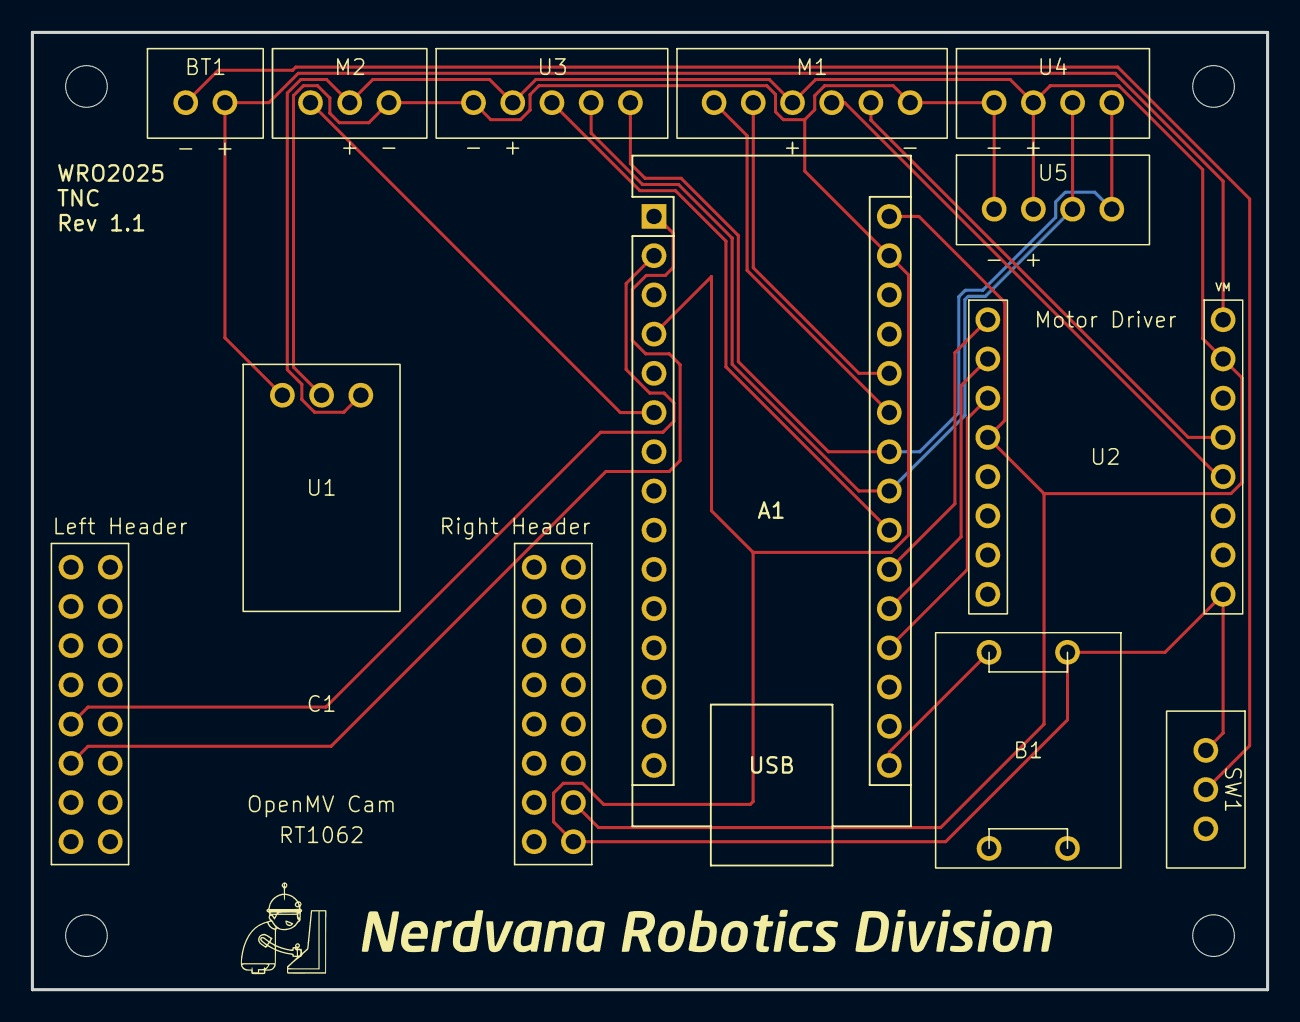
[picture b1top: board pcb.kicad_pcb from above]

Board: 2 copper layers, 80.0 x 62.0 mm, 12 parts (0 on the bottom side), 18 nets.

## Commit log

2026-05-31 fork of last year's repo
2026-06-02 Increase minimum turn radius from 150mm to 175mm
2026-06-11 docs: add Andrei to the team and document this season's software
    Write up the work that went into the robot this year: the WiFi pit dashboard, the drift-free 1000 Hz gyro with continuous zero-rate update, the self-calibrating steering center, and our own dead-reck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
2026-06-11 Revise team member details in README.md
    Updated team member information for Orășeanu Andrei and Priboi Luca Mihai, including age, school/university, and descriptions.
2026-06-11 feat: add on-board localization and drift-free gyro
    Move the heading to a 1000 Hz sample with a continuous zero-rate update so it stops drifting over a run, and add a dead-reckoning localization module that tracks (x, y) on the mat and records the dri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

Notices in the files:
README.md:
Copyright :
MIT License
Permission is hereby granted, free of charge, to any person obtaining a copy of this software and associated documentation files (the "Software"), to deal in the Software without restriction, including without limitation the rights to use, copy, modify, merge, publish, distribute, sublicense, and/or sell copies of the Software, and to permit persons to whom the Software is furnished to do so, subject to the following conditions:
The above copyright notice and this permission notice shall be included in all copies or substantial portions of the Software.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
